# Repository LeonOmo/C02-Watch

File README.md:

# C02 Watch

A compact air quality monitor which tells me when to open the window, it measures C02 lvls with a SCD40 and shows the status on a oled display 

## Why does it exist

- Compact build: I wanted to build something really small all my other Projects were always so chunky
- Sensors: Building with more and more sensors and understanding more about them. With all my projects with sensors i now understand some of the electrical componets in my household.
- 3D Printer: High C02 Lvls can make you unfocused yet you cant see it so i made something where i know when to ventilate.

## Features

- WiFi value sending: Sends a message if you should ventilate. (Only sends when you need to ventilate)
- Compactness: Its overall really small and could fit in your pocket
- Oled Display: A Small Oled display, displaying the Humidity, Temperature and C02.
- Is able to read C02, Humidity and Temperature  

## C02 Lvls

| C02 ppm | Status |
|:---|:---|
| < 800 | Good! |
| 800 - 1000 | Ventilate soon |
| 1000 - 1400 | Ventilate |
| > 1400 | OPEN THE WINDOW! |

## BOM

|  |  |
|:---|:---|
|  |  |
|  |  |
|  |  |
|  |  |

## Tools

- KiCAD (PCB / Schematic)
- Onshape (Case)
- Arduino IDE (Firmware / Code)

## Schematic

## PCB

## Case

## Firmware

## Extras

Credits
- OmoCat (Silkscreen on my PCB not in the files!)

## Bonus

Idea Scatch

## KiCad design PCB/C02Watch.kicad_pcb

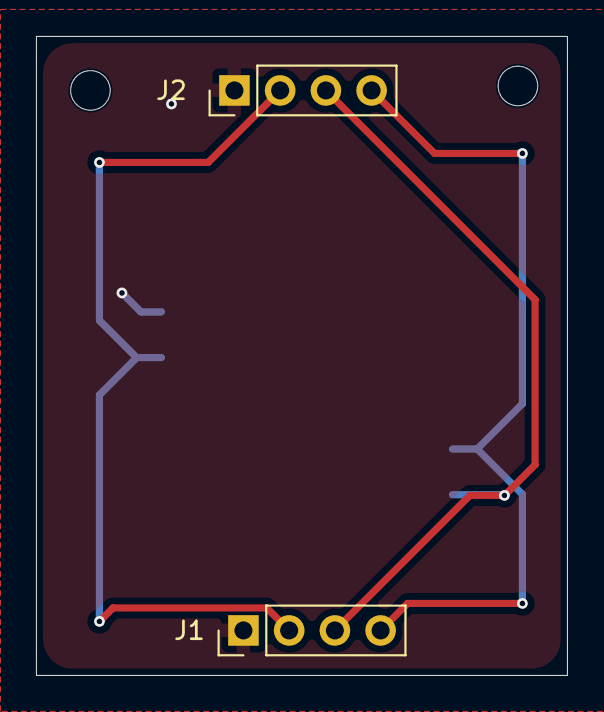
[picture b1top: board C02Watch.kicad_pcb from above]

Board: 2 copper layers, 29.5 x 35.5 mm, 5 parts (1 on the bottom side), 4 nets.

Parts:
H1, H2: MountingHole; MountingHole_2.2mm_M2
J1, J2: Conn_01x04; PinHeader_1x04_P2.54mm_Vertical
U1: XIAO-ESP32-C3-SMD

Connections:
+3.3V: J1.2, J2.2, U1.12 (3V3_OUT)
/SCL: J1.3, J2.3, U1.6 (D5)
/SDA: J1.4, J2.4, U1.5 (D4)
GND: J1.1, J2.1, U1.13 (GND)
